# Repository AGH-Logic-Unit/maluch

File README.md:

## mALUch - 16 bit simple CPU

mALUch is a simple 16 bit cpu, created mostly as a design exercise 

## Running Simulation and Compiling Tools
To compile simulator it is necessary to have ncurses installed  

All that is necessary to compile existing tooling is
```
make init
```

then assemble test program as 
```
./assemble.sh Progs/os_test.cpp out.bin
```

and finally run it as 
```
./simulate out.bin
```

to get list of commands type
```
help
```
to switch between windows use TAB

## Assembler  
To use assembler it is necessary to have fasmg installed

The assembler is implemented as a fasmg .inc file, so to write your own program you have to have `include "path/to/maluch.inc"` included in your file.  
To just do `include "maluch.inc"` make sure to add the path to maluch.inc to an environment variable called INCLUDE.

To compile a program do
```bash
fasmg main.asm [output]
```
The output name is optional, the default is the name of the input file sans the extension.

## Physical Implementation
work in progress 😎

## Software Implementation
in Simulator/  
  
mostly straightforward implementation with no interesting quirks, type `help` for list of commands, use `tab` to switch between COMMANDS window and SCREEN window.

## Authors
### ISA
[@Racuun](https://github.com/Racuun)  
[@sarvl](https://github.com/sarvl) 

### Hardware

#### FPGA
[@Antoni-S](https://github.com/Antoni-S)  
[@didlox1](https://github.com/didlox1)  
[@K-Walega-AGH](https://github.com/K-Walega-AGH)  
[@Racuun](https://github.com/Racuun)   
[@xKraZx](https://github.com/xKraZx)  

#### PCB
[@Bercikowsky](https://github.com/Bercikowsky)  
[@Jasiopi](https://github.com/Jasiopi)  
[@MerlinTheProgrammist](https://github.com/MerlinTheProgramist)  
[@Rudgosz](https://github.com/Rudgosz)  
[@sarvl](https://github.com/sarvl)  

### Software
[@PieVieRo](https://github.com/PieVieRo)  
[@sarvl](https://github.com/sarvl)

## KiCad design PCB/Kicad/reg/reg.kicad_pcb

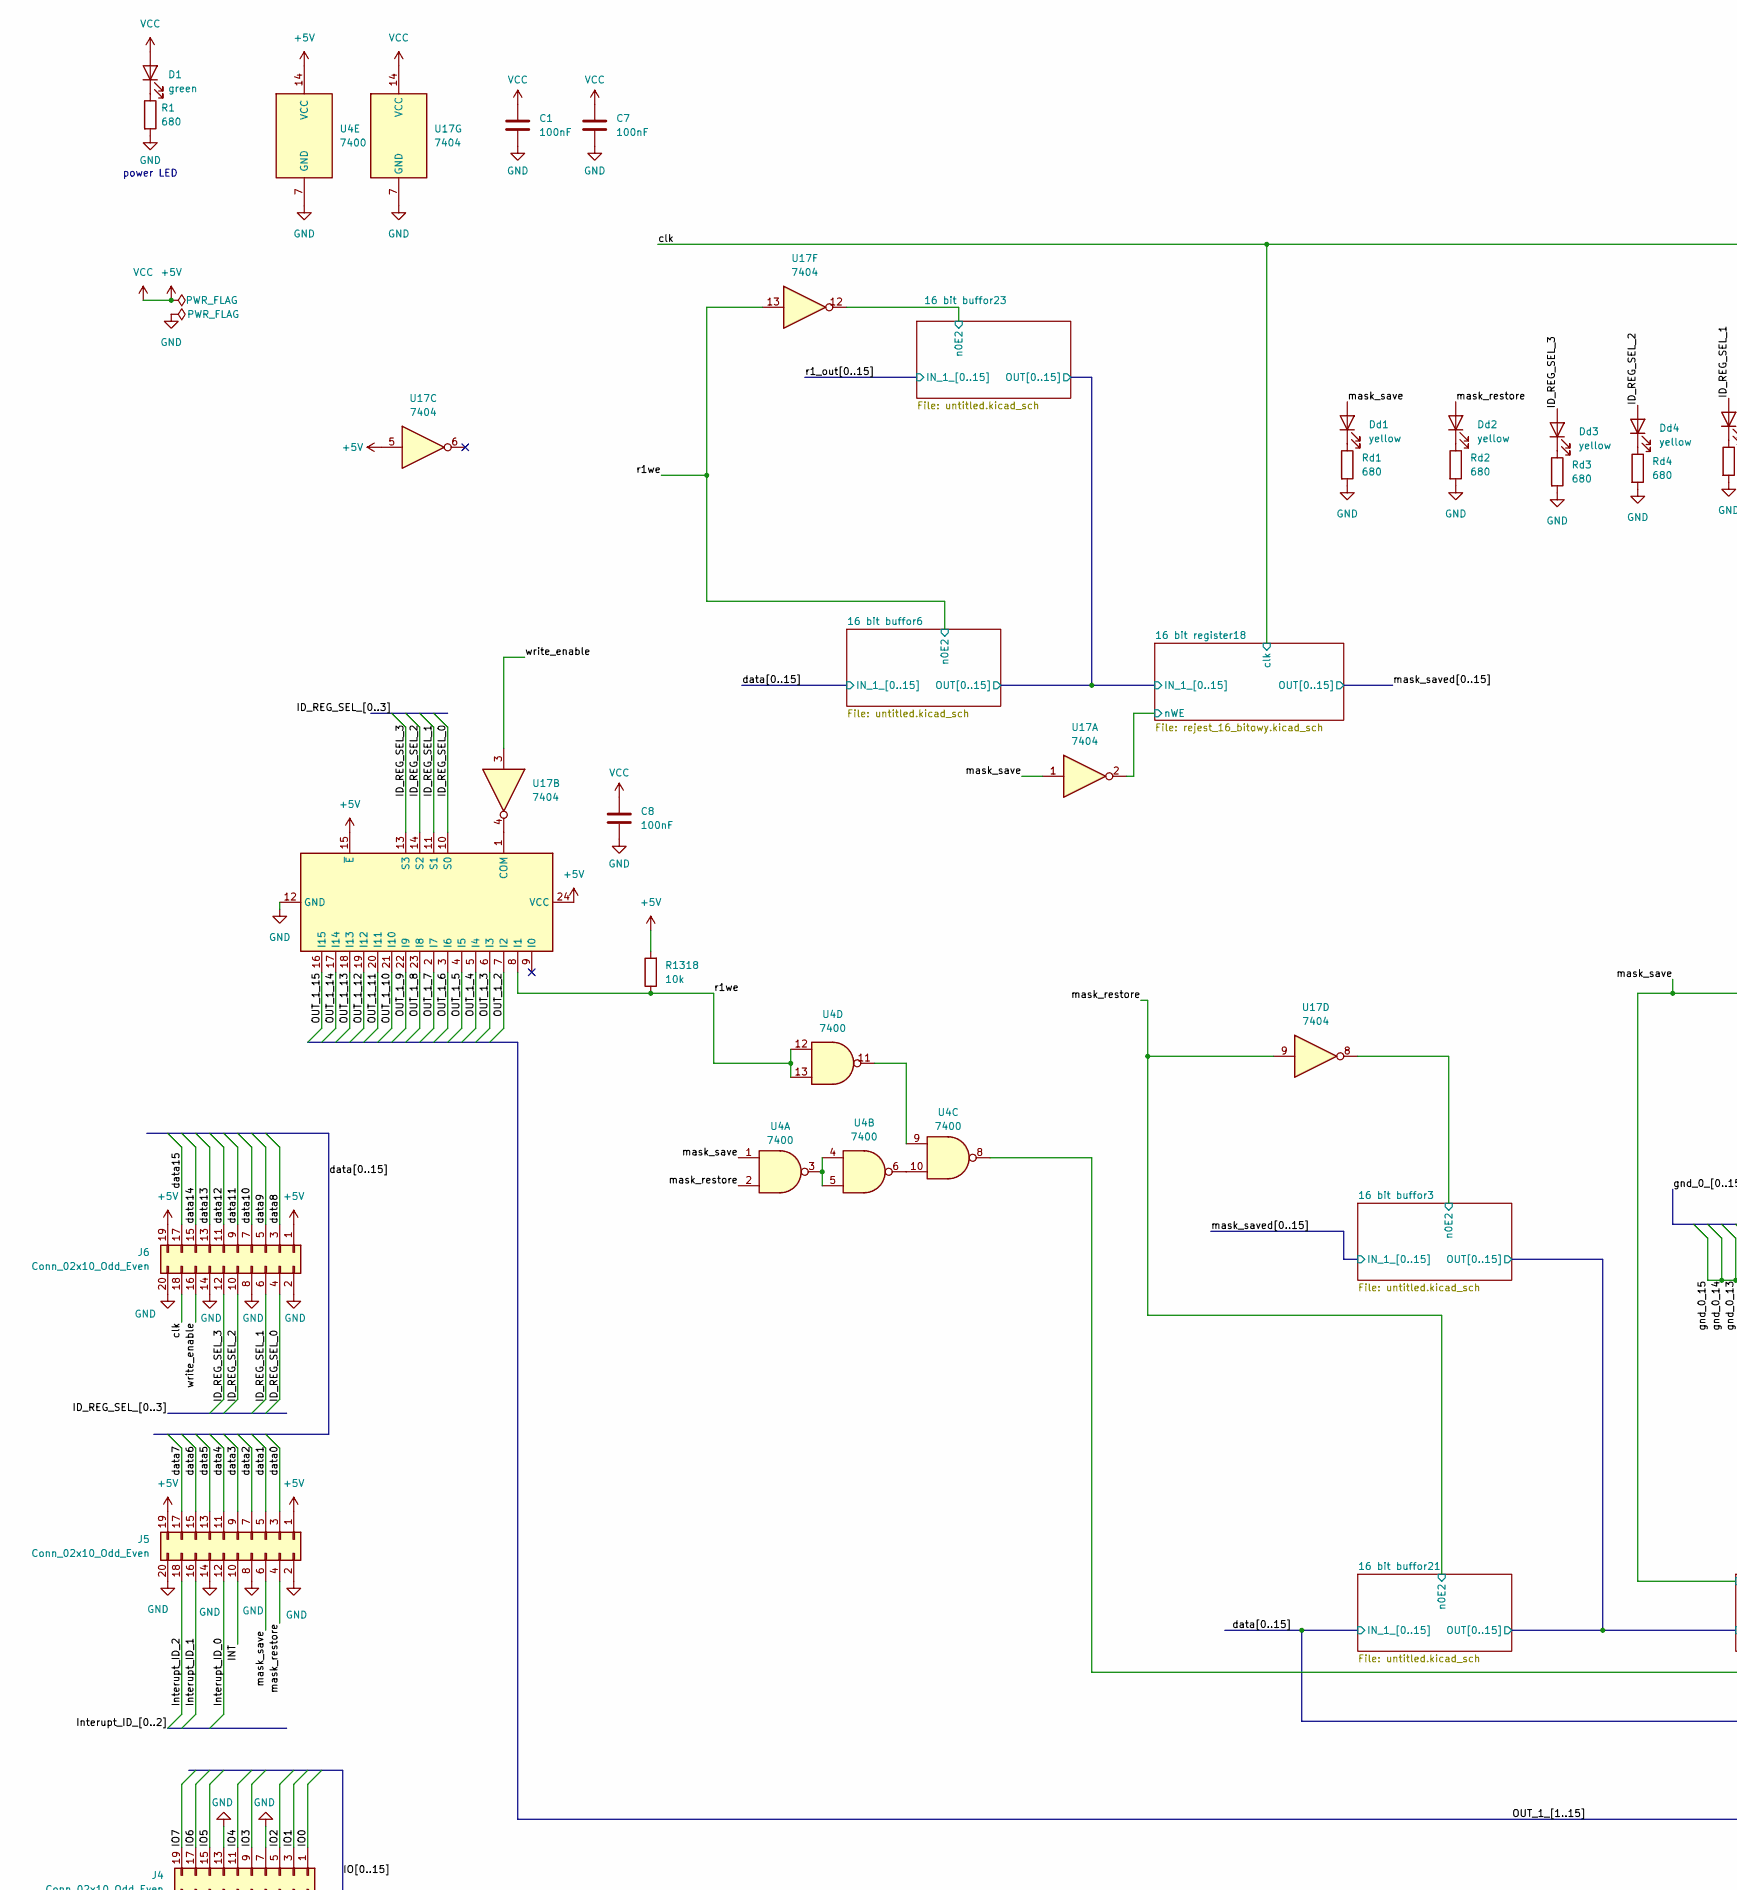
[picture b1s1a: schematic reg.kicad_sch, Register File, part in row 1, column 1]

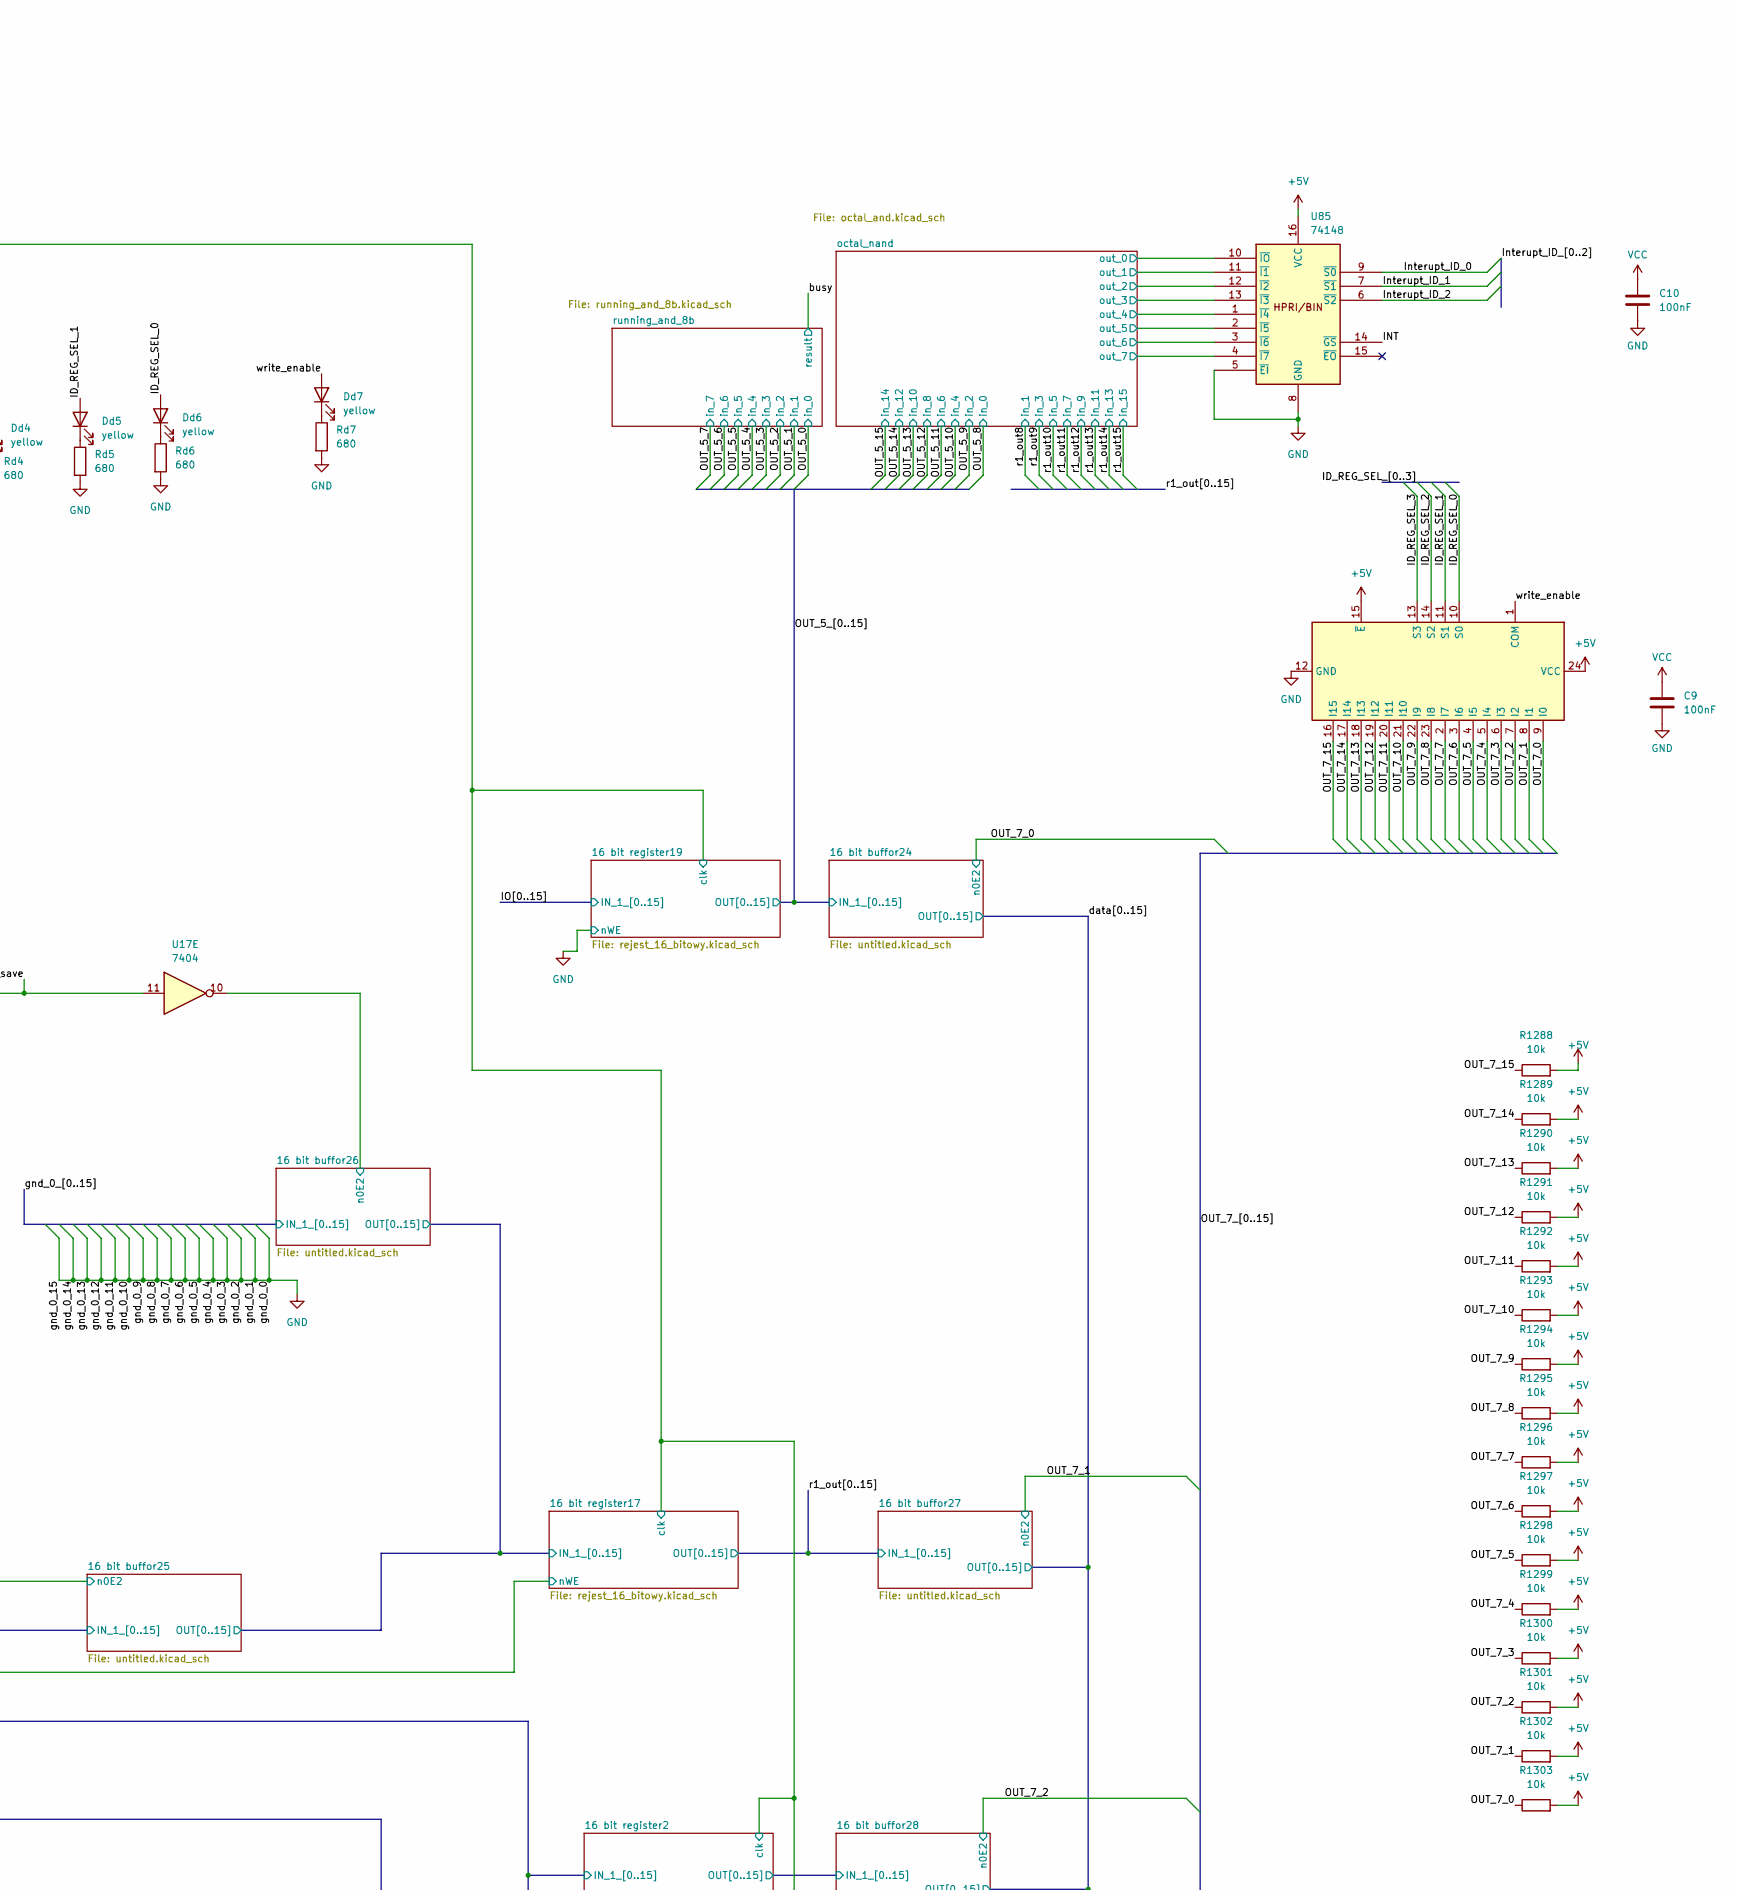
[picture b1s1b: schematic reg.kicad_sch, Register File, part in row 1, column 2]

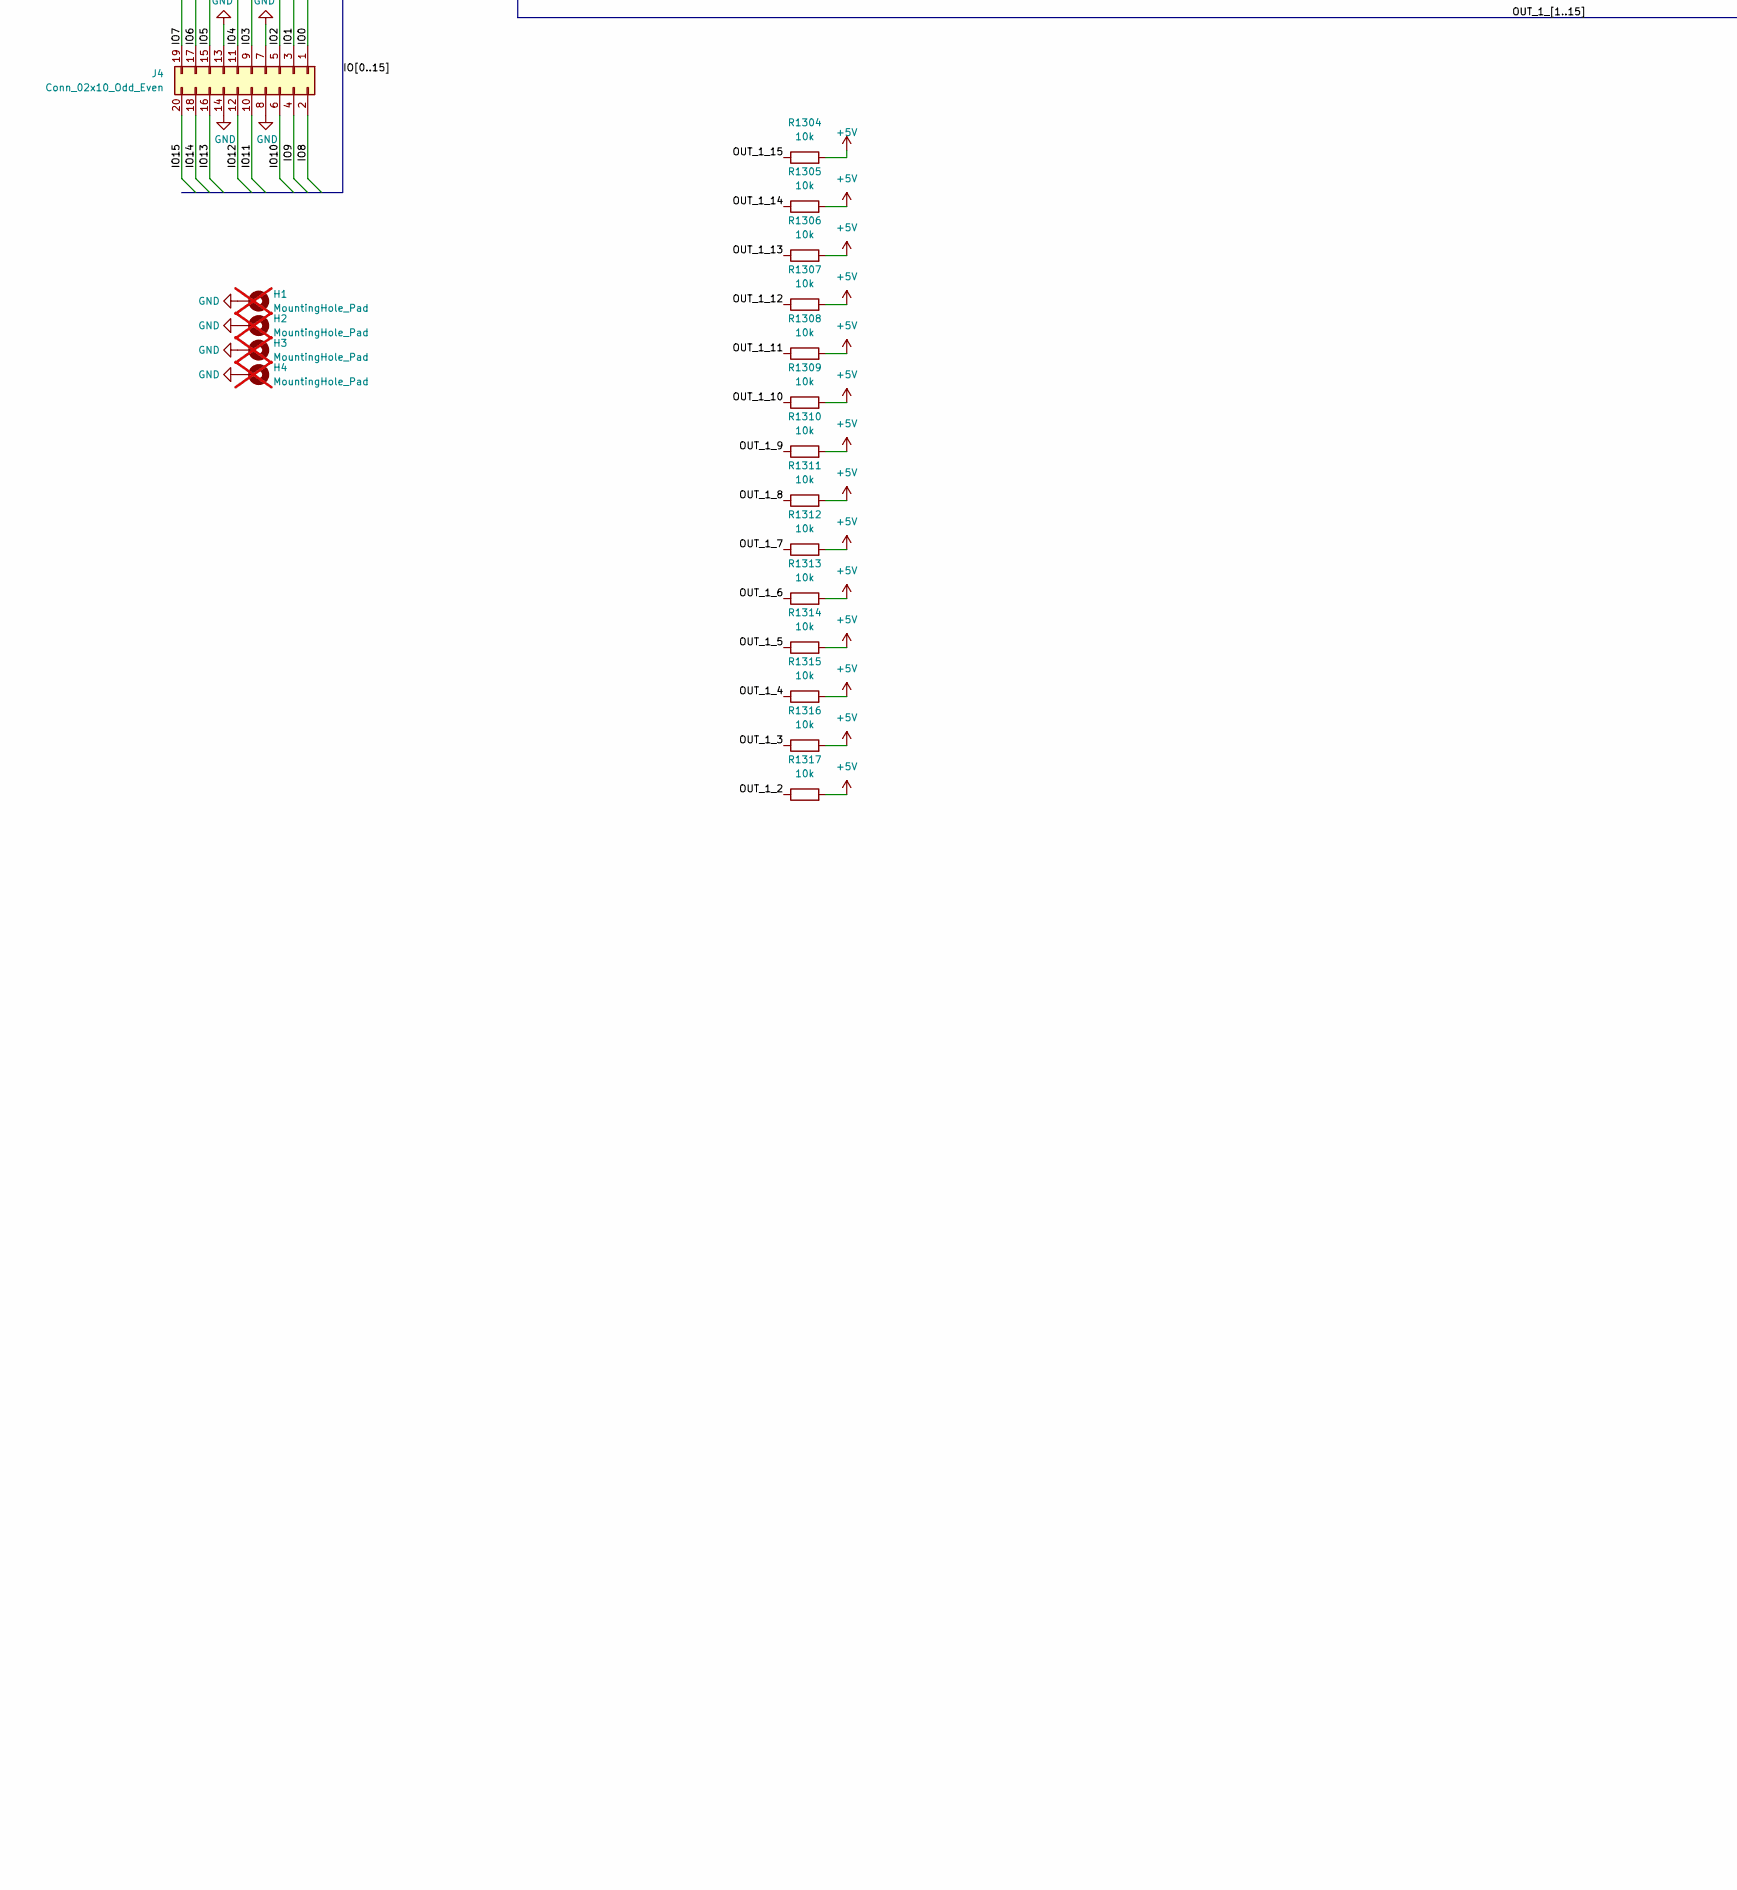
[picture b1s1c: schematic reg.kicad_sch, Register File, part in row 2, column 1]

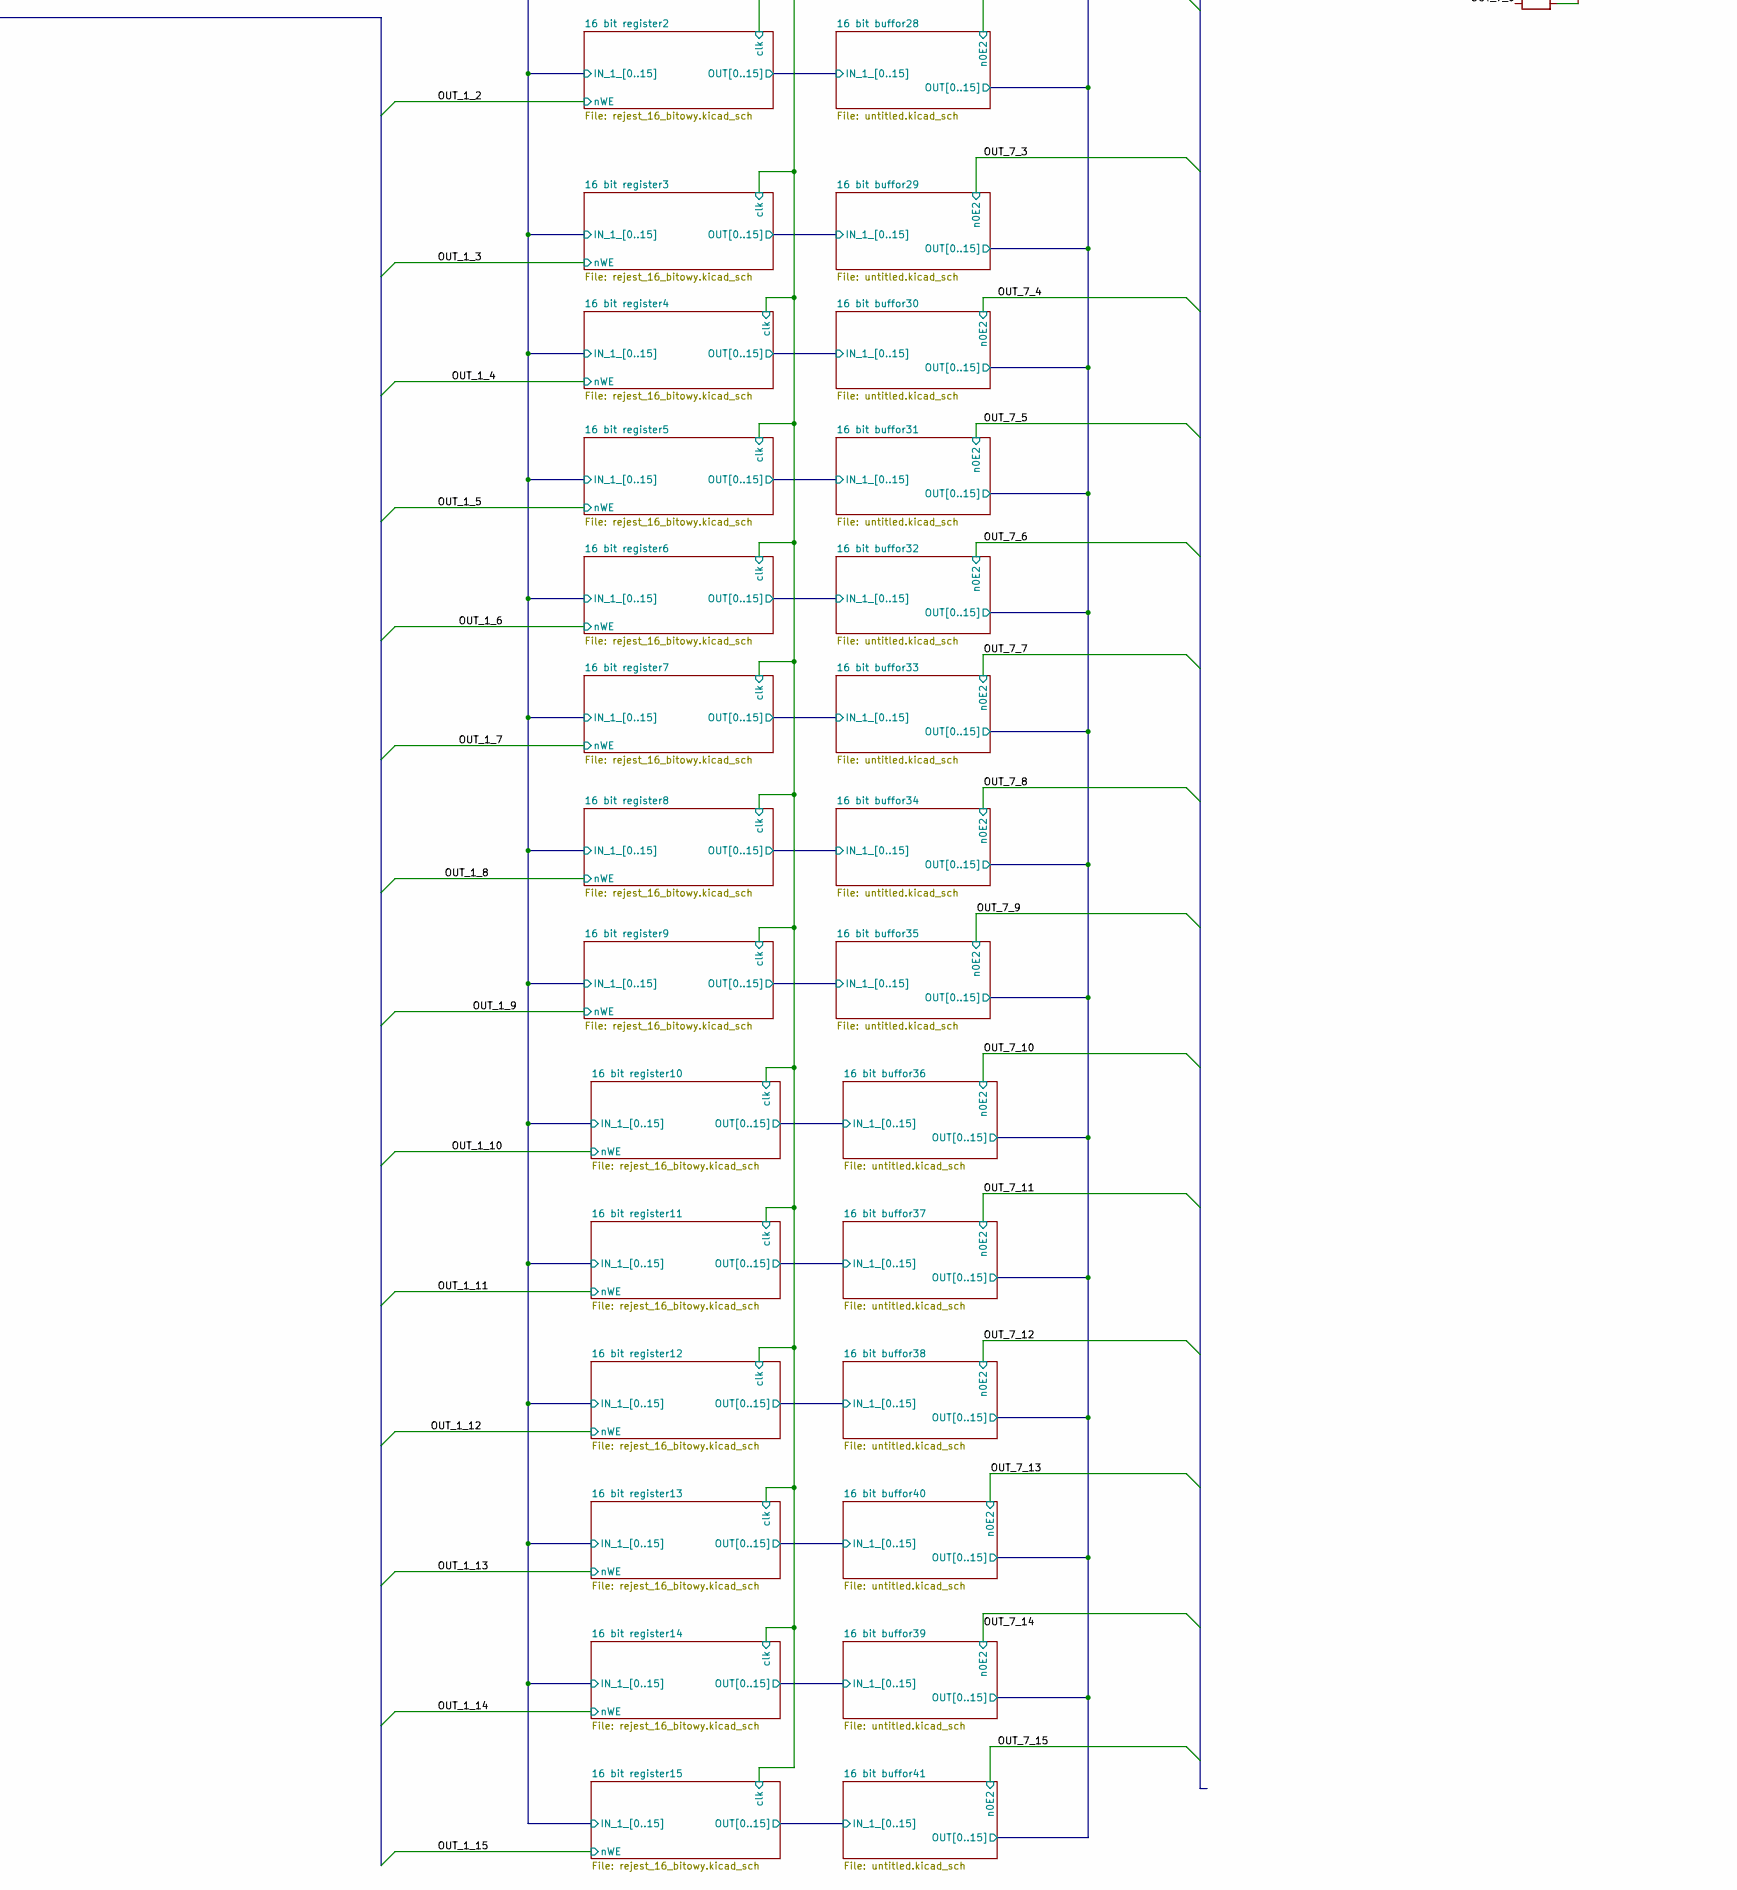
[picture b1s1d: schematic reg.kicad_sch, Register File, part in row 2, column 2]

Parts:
C1, C7, C8, C9, C10: 100nF; C_0402_1005Metric
D1: green; D_0603_1608Metric
Dd1, Dd2, Dd3, Dd4, Dd5, Dd6, Dd7: yellow; LED_0603_1608Metric
H1, H2, H3, H4: MountingHole_Pad; MountingHole_2.2mm_M2_DIN965_Pad; not fitted
J4, J5, J6: Conn_02x10_Odd_Even; PinHeader_2x10_P2.54mm_Horizontal
R1: 680; R_0402_1005Metric
R1288, R1289, R1290, R1291, R1292, R1293, R1294, R1295, R1296, R1297, R1298, R1299, R1300, R1301, R1302, R1303, R1304, R1305, R1306, R1307, R1308, R1309, R1310, R1311, R1312, R1313, R1314, R1315, R1316, R1317, R1318: 10k; R_0402_1005Metric
Rd1, Rd2, Rd3, Rd4, Rd5, Rd6, Rd7: 680; R_0402_1005Metric
U4: 7400; SO-14_3.9x8.65mm_P1.27mm
U17: 7404; SO-14_3.9x8.65mm_P1.27mm
U29, U30: 744067; TSSOP-24_4.4x7.8mm_P0.65mm
U85: 74148; SOIC-16_3.9x9.9mm_P1.27mm

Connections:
+5V: C1.1, C7.1, C8.1, C9.1, C10.1, D1.2 (A), J5.1, J5.19, J6.1, J6.19, R1288.2, R1289.2, R1290.2, R1291.2, R1292.2, R1293.2, R1294.2, R1295.2, R1296.2, R1297.2, R1298.2, R1299.2, R1300.2, R1301.2, R1302.2, R1303.2, R1304.2, R1305.2, R1306.2, R1307.2, R1308.2, R1309.2, R1310.2, R1311.2, R1312.2, R1313.2, R1314.2, R1315.2, R1316.2, R1317.2, R1318.2, U4.14 (VCC), U17.5, U17.14 (VCC), U29.15 (~E), U29.24 (VCC), U30.15 (~E), U30.24 (VCC), U85.16 (VCC); also elsewhere on the board
/16 bit buffor3/n0E2: U17.8; also elsewhere on the board
/16 bit buffor23/n0E2: U17.12; also elsewhere on the board
/16 bit buffor26/n0E2: U17.10; also elsewhere on the board
/16 bit register17/nWE: U4.8; also elsewhere on the board
/16 bit register18/nWE: U17.2; also elsewhere on the board
/ID_REG_SEL_0: Dd6.2 (A), J6.4, U29.10 (S0), U30.10 (S0)
/ID_REG_SEL_1: Dd5.2 (A), J6.6, U29.11 (S1), U30.11 (S1)
/ID_REG_SEL_2: Dd4.2 (A), J6.10, U29.14 (S2), U30.14 (S2)
/ID_REG_SEL_3: Dd3.2 (A), J6.12, U29.13 (S3), U30.13 (S3)
/INT: J5.10, U85.14 (~GS)
/IO0: J4.1; also elsewhere on the board
/IO1: J4.3; also elsewhere on the board
/IO2: J4.5; also elsewhere on the board
/IO3: J4.9; also elsewhere on the board
/IO4: J4.11; also elsewhere on the board
/IO5: J4.15; also elsewhere on the board
/IO6: J4.17; also elsewhere on the board
/IO7: J4.19; also elsewhere on the board
/IO8: J4.2; also elsewhere on the board
/IO9: J4.4; also elsewhere on the board
/IO10: J4.6; also elsewhere on the board
/IO11: J4.10; also elsewhere on the board
/IO12: J4.12; also elsewhere on the board
/IO13: J4.16; also elsewhere on the board
/IO14: J4.18; also elsewhere on the board
/IO15: J4.20; also elsewhere on the board
/Interupt_ID_0: J5.12, U85.9 (~S0)
/Interupt_ID_1: J5.16, U85.7 (~S1)
/Interupt_ID_2: J5.18, U85.6 (~S2)
/OUT_1_2: R1317.1, U29.7 (I2); also elsewhere on the board
/OUT_1_3: R1316.1, U29.6 (I3); also elsewhere on the board
/OUT_1_4: R1315.1, U29.5 (I4); also elsewhere on the board
/OUT_1_5: R1314.1, U29.4 (I5); also elsewhere on the board
/OUT_1_6: R1313.1, U29.3 (I6); also elsewhere on the board
/OUT_1_7: R1312.1, U29.2 (I7); also elsewhere on the board
/OUT_1_8: R1311.1, U29.23 (I8); also elsewhere on the board
/OUT_1_9: R1310.1, U29.22 (I9); also elsewhere on the board
/OUT_1_10: R1309.1, U29.21 (I10); also elsewhere on the board
/OUT_1_11: R1308.1, U29.20 (I11); also elsewhere on the board
/OUT_1_12: R1307.1, U29.19 (I12); also elsewhere on the board
/OUT_1_13: R1306.1, U29.18 (I13); also elsewhere on the board
/OUT_1_14: R1305.1, U29.17 (I14); also elsewhere on the board
/OUT_1_15: R1304.1, U29.16 (I15); also elsewhere on the board
/OUT_7_0: R1303.1, U30.9 (I0); also elsewhere on the board
/OUT_7_1: R1302.1, U30.8 (I1); also elsewhere on the board
/OUT_7_2: R1301.1, U30.7 (I2); also elsewhere on the board
/OUT_7_3: R1300.1, U30.6 (I3); also elsewhere on the board
/OUT_7_4: R1299.1, U30.5 (I4); also elsewhere on the board
/OUT_7_5: R1298.1, U30.4 (I5); also elsewhere on the board
/OUT_7_6: R1297.1, U30.3 (I6); also elsewhere on the board
/OUT_7_7: R1296.1, U30.2 (I7); also elsewhere on the board
/OUT_7_8: R1295.1, U30.23 (I8); also elsewhere on the board
/OUT_7_9: R1294.1, U30.22 (I9); also elsewhere on the board
/OUT_7_10: R1293.1, U30.21 (I10); also elsewhere on the board
/OUT_7_11: R1292.1, U30.20 (I11); also elsewhere on the board
/OUT_7_12: R1291.1, U30.19 (I12); also elsewhere on the board
/OUT_7_13: R1290.1, U30.18 (I13); also elsewhere on the board
/OUT_7_14: R1289.1, U30.17 (I14); also elsewhere on the board
/OUT_7_15: R1288.1, U30.16 (I15); also elsewhere on the board
/clk: J6.18; also elsewhere on the board
/data0: J5.3; also elsewhere on the board
/data1: J5.5; also elsewhere on the board
/data2: J5.7; also elsewhere on the board
/data3: J5.9; also elsewhere on the board
/data4: J5.11; also elsewhere on the board
/data5: J5.13; also elsewhere on the board
/data6: J5.15; also elsewhere on the board
/data7: J5.17; also elsewhere on the board
/data8: J6.3; also elsewhere on the board
/data9: J6.5; also elsewhere on the board
/data10: J6.7; also elsewhere on the board
/data11: J6.9; also elsewhere on the board
/data12: J6.11; also elsewhere on the board
/data13: J6.13; also elsewhere on the board
/data14: J6.15; also elsewhere on the board
/data15: J6.17; also elsewhere on the board
/mask_restore: Dd2.2 (A), J5.4, U4.2, U17.9; also elsewhere on the board
/mask_save: Dd1.2 (A), J5.6, U4.1, U17.1, U17.11; also elsewhere on the board
/octal_nand/out_0: U85.10 (~IO); also elsewhere on the board
/octal_nand/out_1: U85.11 (~I1); also elsewhere on the board
/octal_nand/out_2: U85.12 (~I2); also elsewhere on the board
/octal_nand/out_3: U85.13 (~I3); also elsewhere on the board
/octal_nand/out_4: U85.1 (~I4); also elsewhere on the board
/octal_nand/out_5: U85.2 (~I5); also elsewhere on the board
/octal_nand/out_6: U85.3 (~I6); also elsewhere on the board
/octal_nand/out_7: U85.4 (~I7); also elsewhere on the board
/r1we: R1318.1, U4.12, U4.13, U17.13, U29.8 (I1); also elsewhere on the board
/write_enable: Dd7.2 (A), J6.16, U17.3, U30.1 (COM)
GND: C1.2, C7.2, C8.2, C9.2, C10.2, H1.1 (1_1), H2.1 (1_1), H3.1 (1_1), H4.1 (1_1), J4.7, J4.8, J4.13, J4.14, J5.2, J5.8, J5.14, J5.20, J6.2, J6.8, J6.14, J6.20, R1.2, Rd1.2, Rd2.2, Rd3.2, Rd4.2, Rd5.2, Rd6.2, Rd7.2, U4.7 (GND), U17.7 (GND), U29.12 (GND), U30.12 (GND), U85.5 (~EI), U85.8 (GND); also elsewhere on the board
unnamed: D1.1 (K), R1.1
unnamed: Dd1.1 (K), Rd1.1
unnamed: Dd2.1 (K), Rd2.1
unnamed: Dd3.1 (K), Rd3.1
unnamed: Dd4.1 (K), Rd4.1
unnamed: Dd5.1 (K), Rd5.1
unnamed: Dd6.1 (K), Rd6.1
unnamed: Dd7.1 (K), Rd7.1
unnamed: U4.3, U4.4, U4.5
unnamed: U4.6, U4.10
unnamed: U4.9, U4.11
unnamed: U17.4, U29.1 (COM)

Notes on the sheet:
power LED

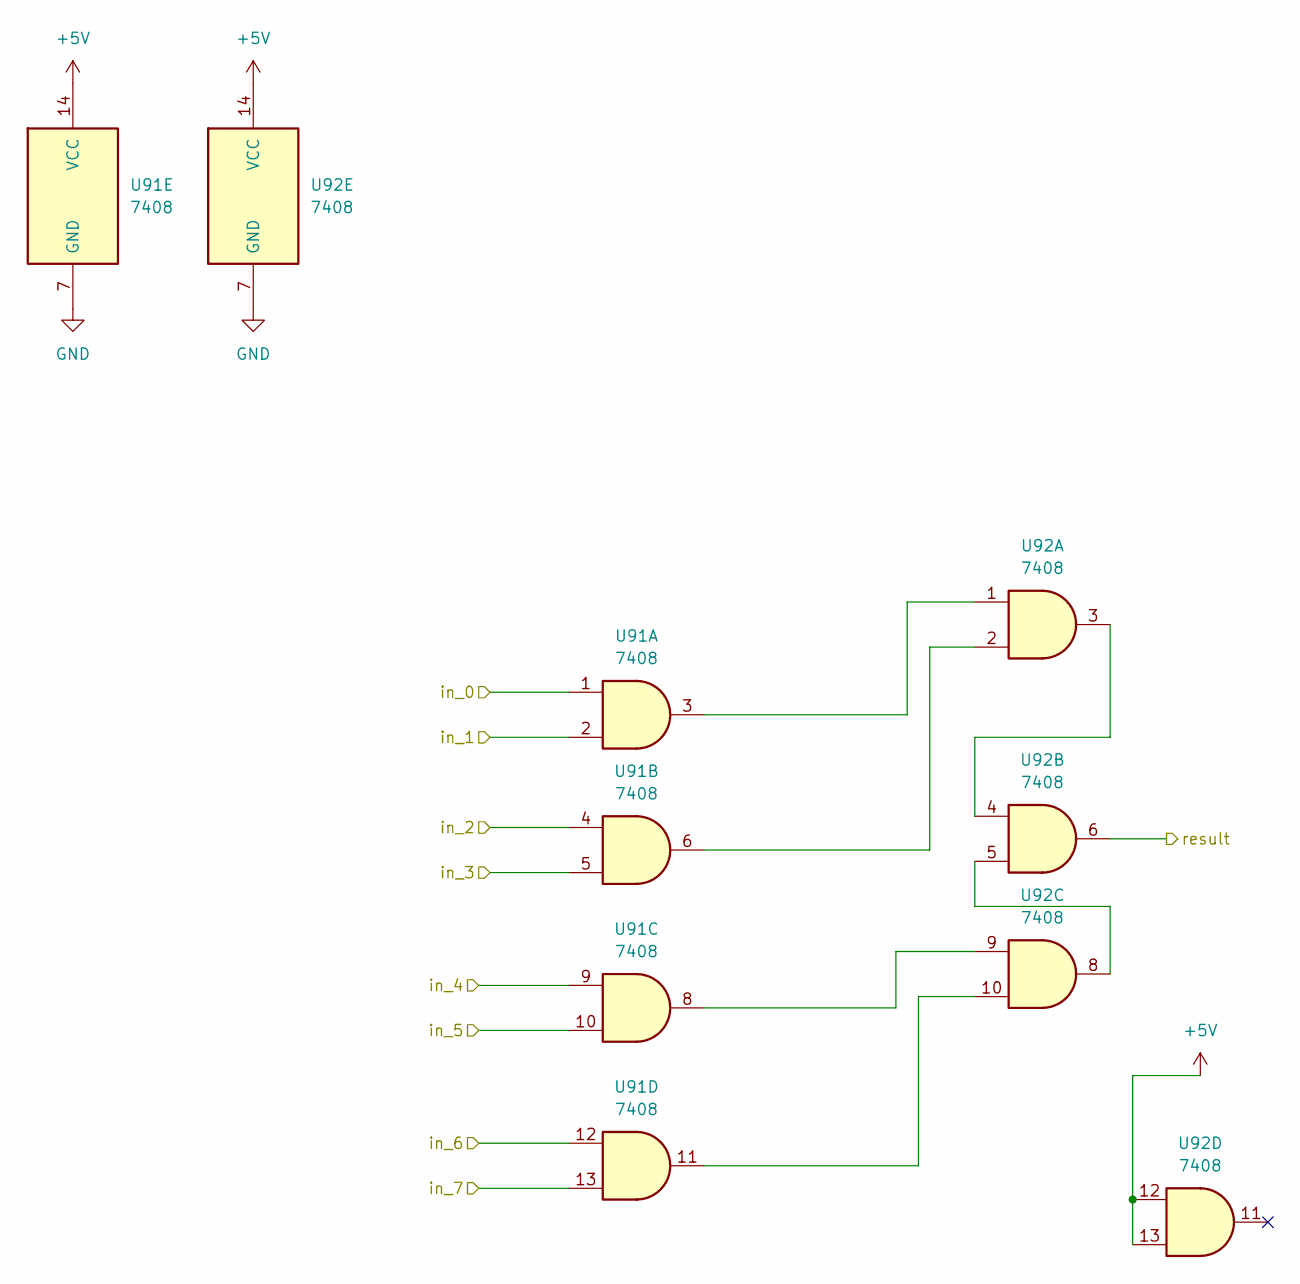
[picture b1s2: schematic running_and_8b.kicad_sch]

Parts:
U91, U92: 7408; SO-14_3.9x8.65mm_P1.27mm

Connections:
+5V: U91.14 (VCC), U92.12, U92.13, U92.14 (VCC); also elsewhere on the board
/OUT_5_0: U91.1; also elsewhere on the board
/OUT_5_1: U91.2; also elsewhere on the board
/OUT_5_2: U91.4; also elsewhere on the board
/OUT_5_3: U91.5; also elsewhere on the board
/OUT_5_4: U91.9; also elsewhere on the board
/OUT_5_5: U91.10; also elsewhere on the board
/OUT_5_6: U91.12; also elsewhere on the board
/OUT_5_7: U91.13; also elsewhere on the board
/busy: U92.6
GND: U91.7 (GND), U92.7 (GND); also elsewhere on the board
unnamed: U91.3, U92.1
unnamed: U91.6, U92.2
unnamed: U91.8, U92.9
unnamed: U91.11, U92.10
unnamed: U92.3, U92.4
unnamed: U92.5, U92.8
